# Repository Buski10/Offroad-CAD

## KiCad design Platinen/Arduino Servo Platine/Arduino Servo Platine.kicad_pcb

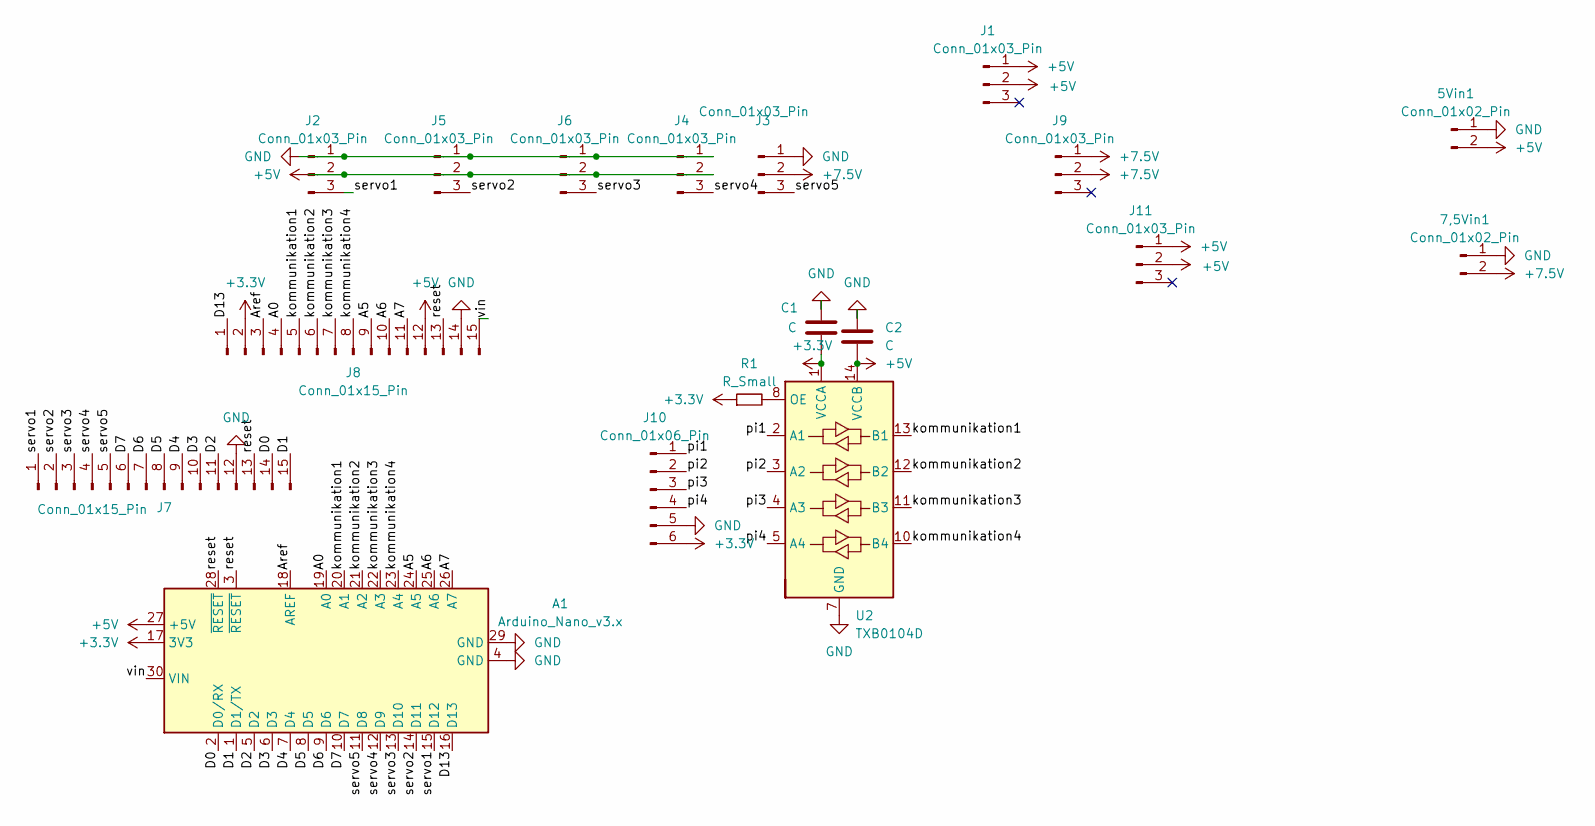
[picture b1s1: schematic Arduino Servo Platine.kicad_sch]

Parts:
5Vin1, 7,5Vin1: Conn_01x02_Pin; Molex_Micro-Fit_3.0_43650-0215_1x02_P3.00mm_Vertical
A1: Arduino_Nano_v3.x; Arduino_Nano
C1, C2: C; C_0805_2012Metric_Pad1.18x1.45mm_HandSolder
J1, J9, J11: Conn_01x03_Pin; SW_100SP1T1B1M1QEH
J2, J3, J4, J5, J6: Conn_01x03_Pin; JST_PH_B3B-PH-K_1x03_P2.00mm_Vertical
J7, J8: Conn_01x15_Pin; PinSocket_1x15_P2.54mm_Vertical
J10: Conn_01x06_Pin; JST_PH_B6B-PH-K_1x06_P2.00mm_Vertical
R1: R_Small; R_0805_2012Metric_Pad1.20x1.40mm_HandSolder
U2: TXB0104D; D14

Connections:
+3.3V: A1.17 (3V3), C1.2, J8.2, J10.6, R1.1, U2.1 (VCCA)
+5V: 5Vin1.2, A1.27 (+5V), C2.2, J1.1, J1.2, J2.2, J4.2, J5.2, J6.2, J8.12, J11.1, J11.2, U2.14 (VCCB)
+7.5V: 7,5Vin1.2, J3.2, J9.1, J9.2
/A0: A1.19 (A0), J8.4
/A5: A1.24 (A5), J8.9
/A6: A1.25 (A6), J8.10
/A7: A1.26 (A7), J8.11
/Aref: A1.18 (AREF), J8.3
/D0: A1.2 (D0/RX), J7.14
/D1: A1.1 (D1/TX), J7.15
/D2: A1.5 (D2), J7.11
/D3: A1.6 (D3), J7.10
/D4: A1.7 (D4), J7.9
/D5: A1.8 (D5), J7.8
/D6: A1.9 (D6), J7.7
/D7: A1.10 (D7), J7.6
/D13: A1.16 (D13), J8.1
/kommunikation1: A1.20 (A1), J8.5, U2.13 (B1)
/kommunikation2: A1.21 (A2), J8.6, U2.12 (B2)
/kommunikation3: A1.22 (A3), J8.7, U2.11 (B3)
/kommunikation4: A1.23 (A4), J8.8, U2.10 (B4)
/pi1: J10.1, U2.2 (A1)
/pi2: J10.2, U2.3 (A2)
/pi3: J10.3, U2.4 (A3)
/pi4: J10.4, U2.5 (A4)
/reset: A1.3 (~RESET), A1.28 (~RESET), J7.13, J8.13
/servo1: A1.15 (D12), J2.3, J7.1
/servo2: A1.14 (D11), J5.3, J7.2
/servo3: A1.13 (D10), J6.3, J7.3
/servo4: A1.12 (D9), J4.3, J7.4
/servo5: A1.11 (D8), J3.3, J7.5
/vin: A1.30 (VIN), J8.15
GND: 5Vin1.1, 7,5Vin1.1, A1.4 (GND), A1.29 (GND), C1.1, C2.1, J2.1, J3.1, J4.1, J5.1, J6.1, J7.12, J8.14, J10.5, U2.7 (GND)
unnamed: R1.2, U2.8 (OE)

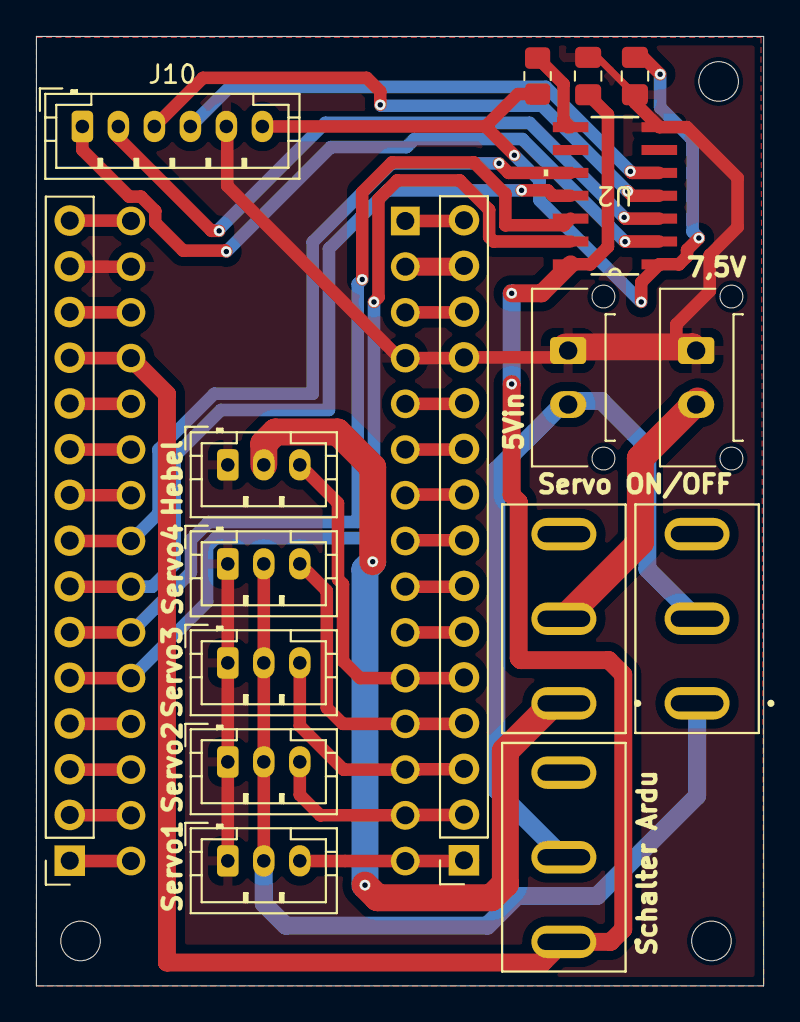
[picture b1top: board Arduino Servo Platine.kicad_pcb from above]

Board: 2 copper layers, 40.4 x 52.8 mm, 18 parts (1 on the bottom side), 34 nets.

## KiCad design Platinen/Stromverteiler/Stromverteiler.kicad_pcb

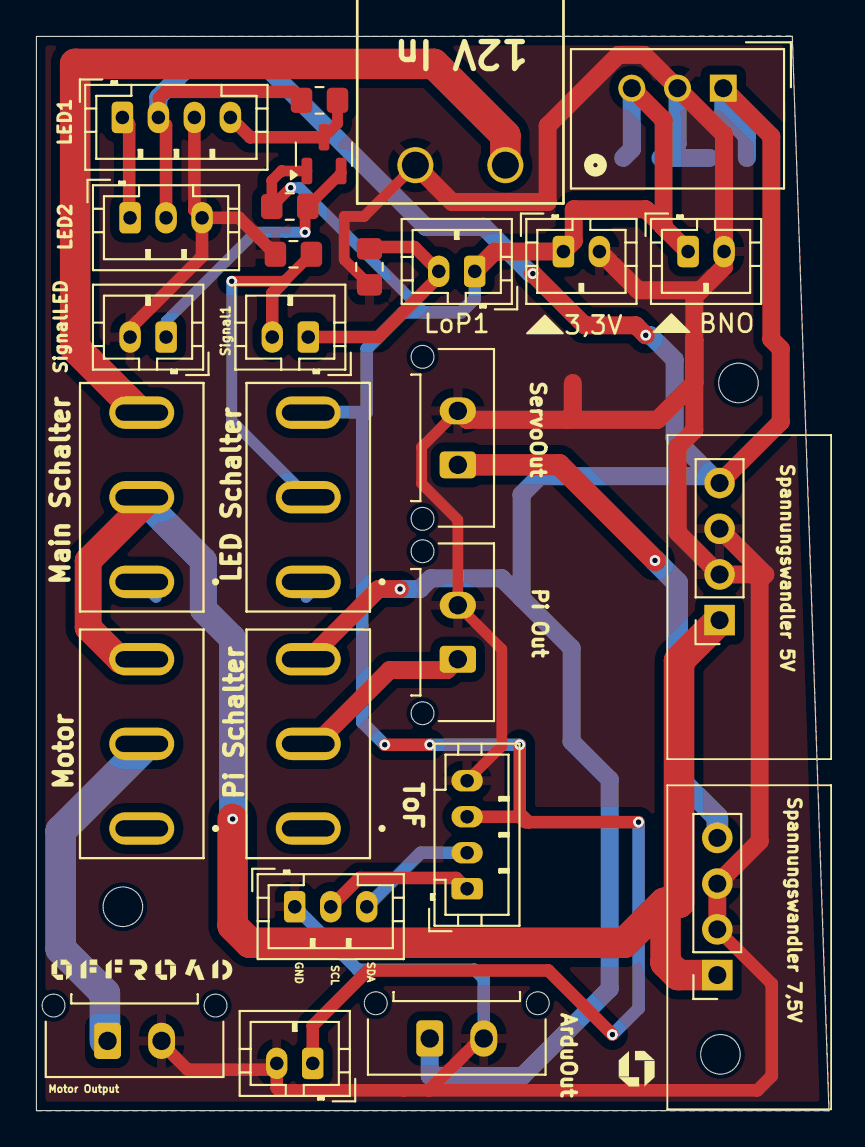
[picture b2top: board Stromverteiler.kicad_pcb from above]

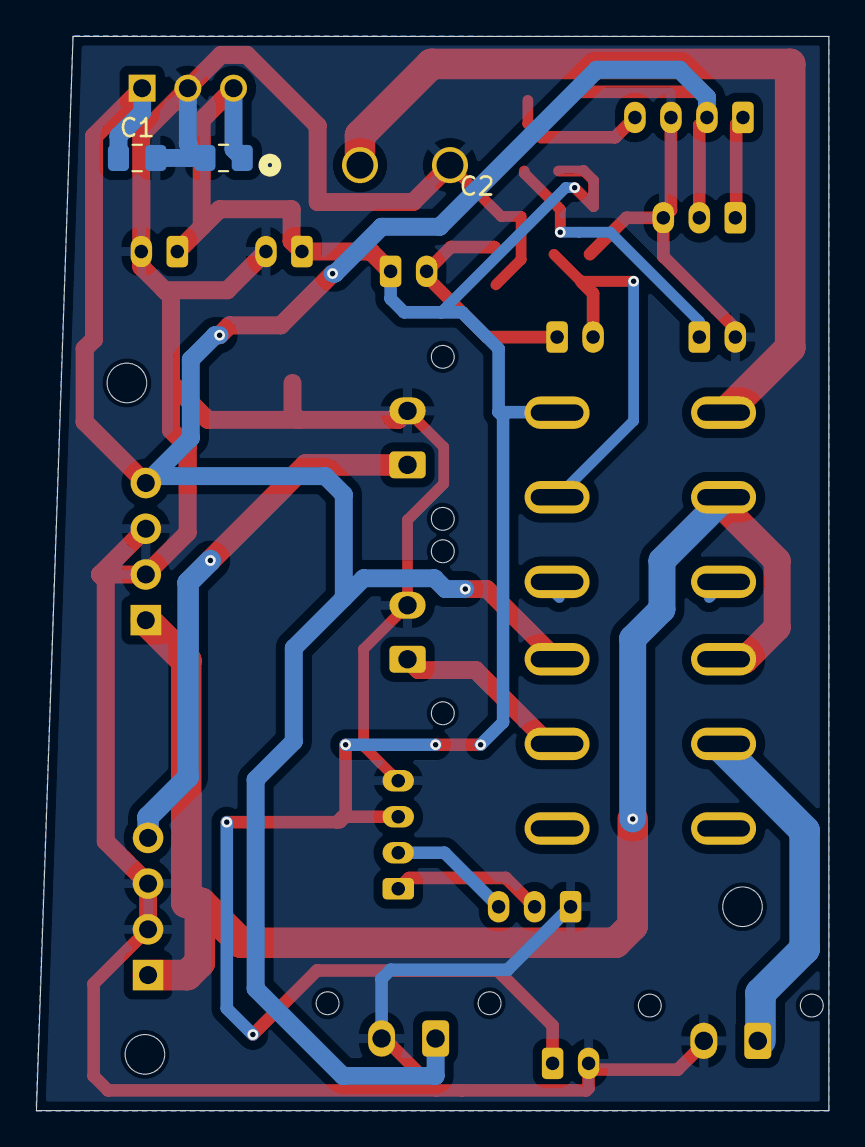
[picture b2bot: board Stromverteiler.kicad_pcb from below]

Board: 2 copper layers, 44.0 x 59.7 mm, 29 parts (2 on the bottom side), 12 nets.

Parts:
3,3V1: Conn_01x02_Pin; JST_PH_B2B-PH-K_1x02_P2.00mm_Vertical
3,3V2: 3,3out; JST_PH_B2B-PH-K_1x02_P2.00mm_Vertical
12Vin1: Conn_01x02_Pin; CONN_31330102_MZC
Arduino1: Conn_01x02_Pin; Molex_Micro-Fit_3.0_43650-0215_1x02_P3.00mm_Vertical
BNO1: Conn_01x02_Pin; JST_PH_B2B-PH-K_1x02_P2.00mm_Vertical
C1, C2: C; C_0805_2012Metric_Pad1.18x1.45mm_HandSolder
J1: Conn_01x03_Pin; JST_PH_B3B-PH-K_1x03_P2.00mm_Vertical
LEDAnzeige1: Conn_01x03_Pin; JST_PH_B3B-PH-K_1x03_P2.00mm_Vertical
LEDring1: Conn_01x04_Pin; JST_PH_B4B-PH-K_1x04_P2.00mm_Vertical
LoP1: Conn_01x02_Pin; JST_PH_B2B-PH-K_1x02_P2.00mm_Vertical
MotorOutput1: Conn_01x02_Pin; Molex_Micro-Fit_3.0_43650-0215_1x02_P3.00mm_Vertical
Output1: Conn_01x02_Pin; Molex_Micro-Fit_3.0_43650-0215_1x02_P3.00mm_Vertical
OutputPi1: Conn_01x02_Pin; Molex_Micro-Fit_3.0_43650-0215_1x02_P3.00mm_Vertical
Q1: BSS138; SOT-23
R1, R6, R7, R8: R_Small; R_0805_2012Metric_Pad1.20x1.40mm_HandSolder
Schalter1LED1, Schalter2Main1, Schalter3Motor1, Schalter4Pi1: Conn_01x03_Pin; SW_100SP1T1B1M1QEH
Signal1: Conn_01x02_Pin; JST_PH_B2B-PH-K_1x02_P2.00mm_Vertical
SignalLED1: Conn_01x02_Pin; JST_PH_B2B-PH-K_1x02_P2.00mm_Vertical
Spannungswandler1, Spannungswandler2: Conn_01x04_Pin; PinSocket_1x04_P2.54mm_Vertical
StemmaToF1: Conn_01x04_Pin; JST_PH_B4B-PH-K_1x04_P2.00mm_Vertical
Wandler1: TSR1-2433E; Converter_DCDC_TRACO_TSR1-xxxxE_THT

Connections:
+3.3V: 3,3V1.1, 3,3V2.1, BNO1.1, C2.2, LoP1.1, Q1.1 (G), R7.1, Schalter1LED1.3, StemmaToF1.3, Wandler1.3 (Vout)
+5V: Arduino1.1, C1.1, LEDAnzeige1.2, LEDring1.2, OutputPi1.1, R8.1, Schalter4Pi1.2, Schalter4Pi1.3, Spannungswandler1.4, Wandler1.1 (Vin)
+7.5V: Output1.1, Spannungswandler2.4
+12V: 12Vin1.1, MotorOutput1.1, Schalter2Main1.2, Schalter2Main1.3, Schalter3Motor1.2, Schalter3Motor1.3, Spannungswandler1.1, Spannungswandler2.1
GND: 3,3V1.2, 3,3V2.2, 12Vin1.2, Arduino1.2, BNO1.2, C1.2, C2.1, J1.1, LEDAnzeige1.3, LEDring1.3, MotorOutput1.2, Output1.2, OutputPi1.2, R1.2, R6.2, SignalLED1.2, Spannungswandler1.2, Spannungswandler1.3, Spannungswandler2.2, Spannungswandler2.3, StemmaToF1.4, Wandler1.2 (GND)
unnamed: J1.2, StemmaToF1.1
unnamed: J1.3, StemmaToF1.2
unnamed: LEDAnzeige1.1, LEDring1.1
unnamed: LEDring1.4, Q1.3 (D), R8.2
unnamed: LoP1.2, R1.1, Signal1.1
unnamed: Q1.2 (S), R7.2, SignalLED1.1
unnamed: R6.1, Schalter1LED1.2, Signal1.2

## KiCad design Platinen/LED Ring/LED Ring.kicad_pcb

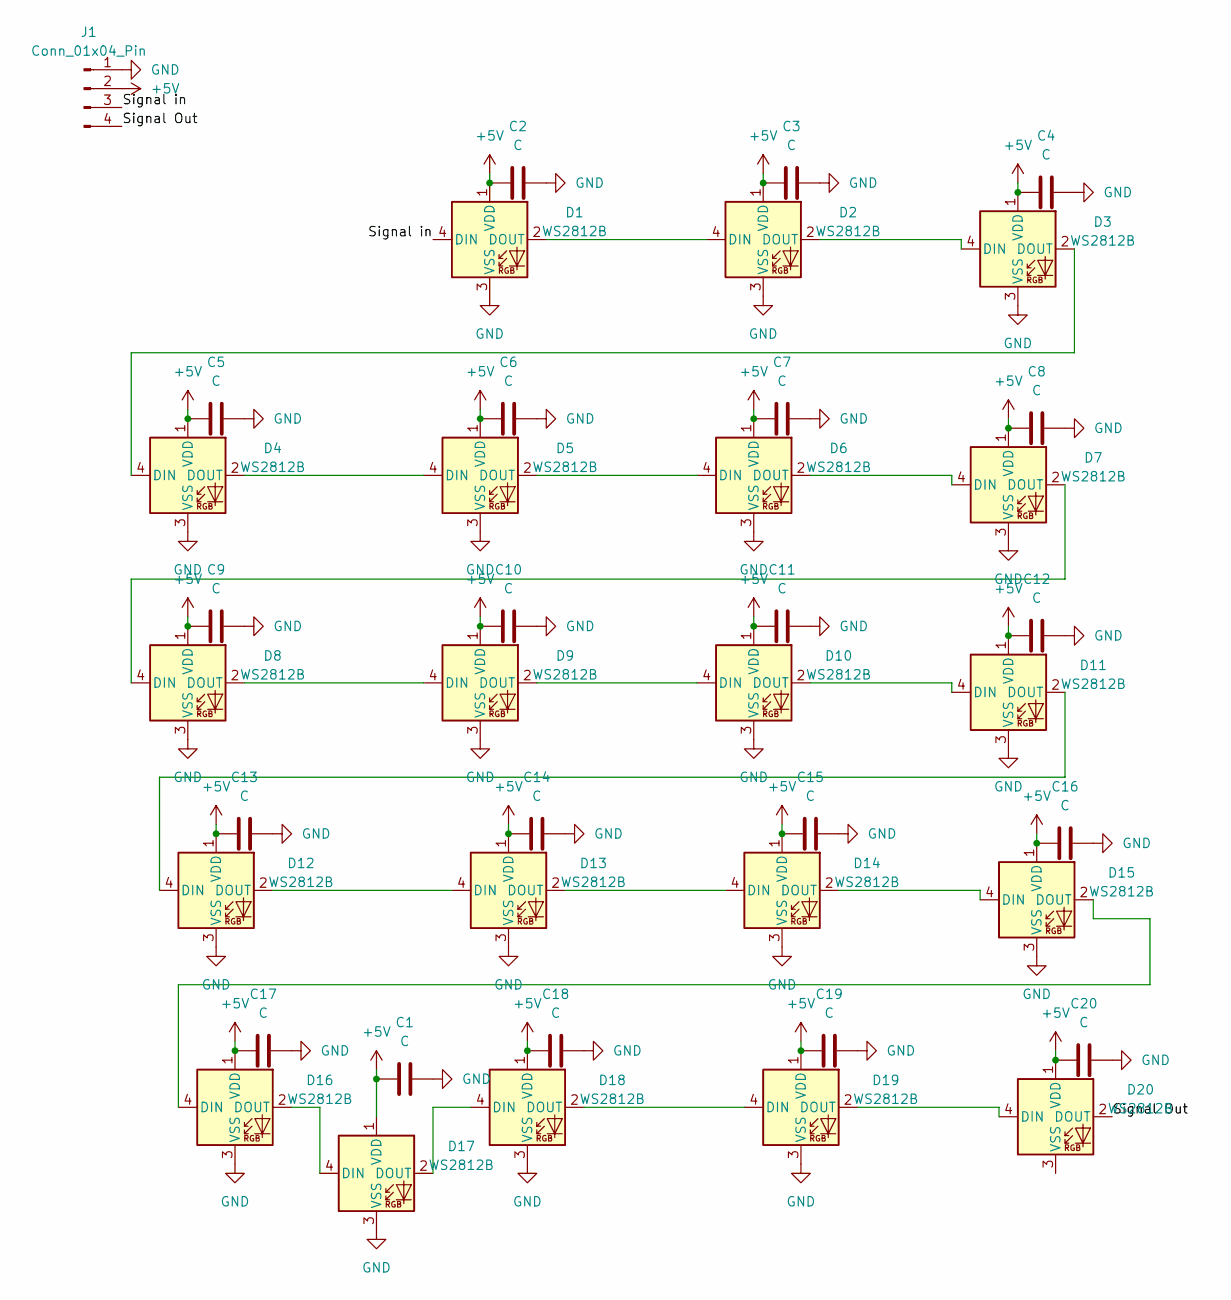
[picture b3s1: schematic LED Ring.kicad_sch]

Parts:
C1, C2, C3, C4, C5, C6, C7, C8, C9, C10, C11, C12, C13, C14, C15, C16, C17, C18, C19, C20: C; C_0805_2012Metric_Pad1.18x1.45mm_HandSolder
D1, D2, D3, D4, D5, D6, D7, D8, D9, D10, D11, D12, D13, D14, D15, D16, D17, D18, D19, D20: WS2812B; LED_WS2812B_PLCC4_5.0x5.0mm_P3.2mm
J1: Conn_01x04_Pin; JST_PH_B4B-PH-K_1x04_P2.00mm_Vertical

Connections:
+5V: C1.1, C2.1, C3.1, C4.1, C5.1, C6.1, C7.1, C8.1, C9.1, C10.1, C11.1, C12.1, C13.1, C14.1, C15.1, C16.1, C17.1, C18.1, C19.1, C20.1, D1.1 (VDD), D2.1 (VDD), D3.1 (VDD), D4.1 (VDD), D5.1 (VDD), D6.1 (VDD), D7.1 (VDD), D8.1 (VDD), D9.1 (VDD), D10.1 (VDD), D11.1 (VDD), D12.1 (VDD), D13.1 (VDD), D14.1 (VDD), D15.1 (VDD), D16.1 (VDD), D17.1 (VDD), D18.1 (VDD), D19.1 (VDD), D20.1 (VDD), J1.2
/Signal Out: D20.2 (DOUT), J1.4
/Signal in: D1.4 (DIN), J1.3
GND: C1.2, C2.2, C3.2, C4.2, C5.2, C6.2, C7.2, C8.2, C9.2, C10.2, C11.2, C12.2, C13.2, C14.2, C15.2, C16.2, C17.2, C18.2, C19.2, C20.2, D1.3 (VSS), D2.3 (VSS), D3.3 (VSS), D4.3 (VSS), D5.3 (VSS), D6.3 (VSS), D7.3 (VSS), D8.3 (VSS), D9.3 (VSS), D10.3 (VSS), D11.3 (VSS), D12.3 (VSS), D13.3 (VSS), D14.3 (VSS), D15.3 (VSS), D16.3 (VSS), D17.3 (VSS), D18.3 (VSS), D19.3 (VSS), J1.1
unnamed: D1.2 (DOUT), D2.4 (DIN)
unnamed: D2.2 (DOUT), D3.4 (DIN)
unnamed: D3.2 (DOUT), D4.4 (DIN)
unnamed: D4.2 (DOUT), D5.4 (DIN)
unnamed: D5.2 (DOUT), D6.4 (DIN)
unnamed: D6.2 (DOUT), D7.4 (DIN)
unnamed: D7.2 (DOUT), D8.4 (DIN)
unnamed: D8.2 (DOUT), D9.4 (DIN)
unnamed: D9.2 (DOUT), D10.4 (DIN)
unnamed: D10.2 (DOUT), D11.4 (DIN)
unnamed: D11.2 (DOUT), D12.4 (DIN)
unnamed: D12.2 (DOUT), D13.4 (DIN)
unnamed: D13.2 (DOUT), D14.4 (DIN)
unnamed: D14.2 (DOUT), D15.4 (DIN)
unnamed: D15.2 (DOUT), D16.4 (DIN)
unnamed: D16.2 (DOUT), D17.4 (DIN)
unnamed: D17.2 (DOUT), D18.4 (DIN)
unnamed: D18.2 (DOUT), D19.4 (DIN)
unnamed: D19.2 (DOUT), D20.4 (DIN)

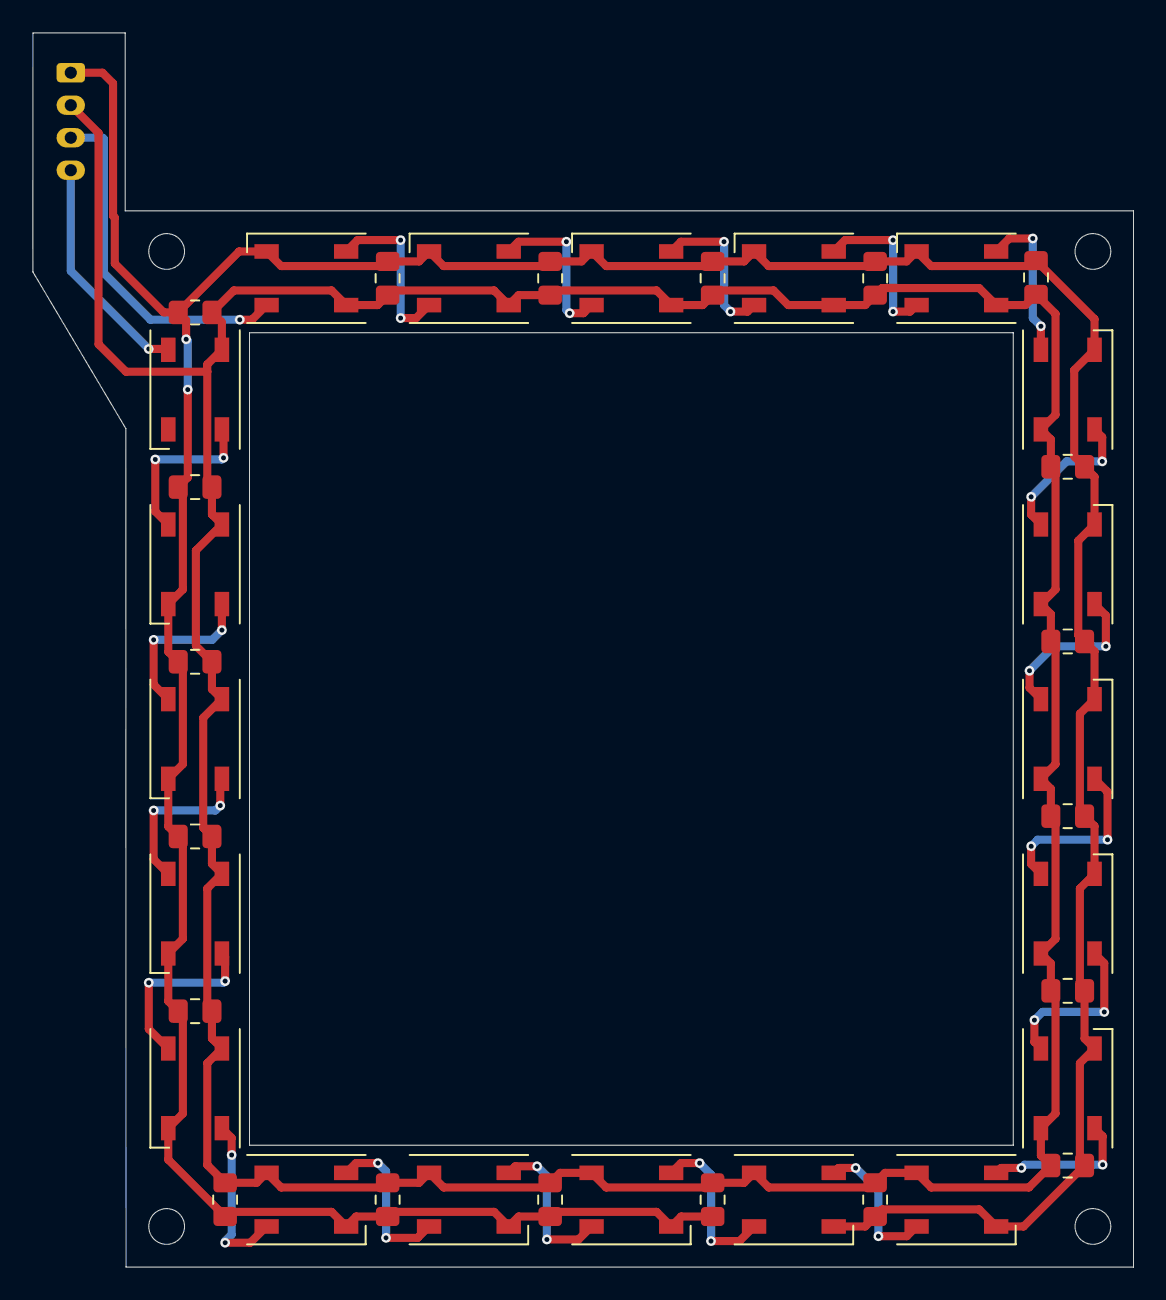
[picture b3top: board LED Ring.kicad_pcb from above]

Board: 2 copper layers, 67.7 x 76.0 mm, 41 parts (1 on the bottom side), 23 nets.

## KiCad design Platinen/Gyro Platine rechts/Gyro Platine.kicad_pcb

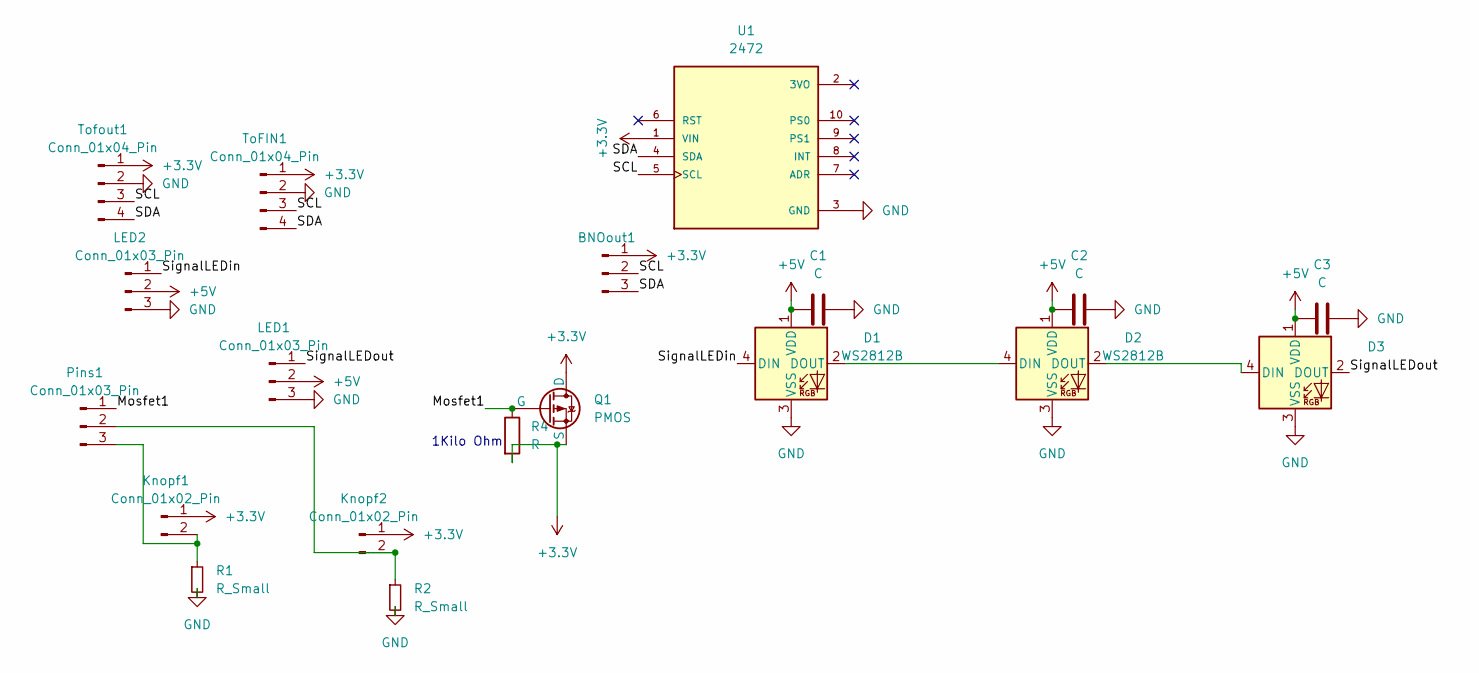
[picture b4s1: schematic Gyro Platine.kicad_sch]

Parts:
BNOout1: Conn_01x03_Pin; JST_PH_B3B-PH-K_1x03_P2.00mm_Vertical
C1, C2, C3: C; C_0805_2012Metric_Pad1.18x1.45mm_HandSolder
D1, D2, D3: WS2812B; LED_WS2812B_PLCC4_5.0x5.0mm_P3.2mm
Knopf1, Knopf2: Conn_01x02_Pin; JST_PH_B2B-PH-K_1x02_P2.00mm_Vertical
LED1, LED2: Conn_01x03_Pin; JST_PH_B3B-PH-K_1x03_P2.00mm_Vertical
Pins1: Conn_01x03_Pin; JST_PH_B3B-PH-K_1x03_P2.00mm_Vertical
Q1: PMOS; SOT-23_IRLML2244TRPBF_INF
R1, R2: R_Small; R_0805_2012Metric_Pad1.20x1.40mm_HandSolder
R4: R; R_0805_2012Metric_Pad1.20x1.40mm_HandSolder
ToFIN1: Conn_01x04_Pin; JST_PH_B4B-PH-K_1x04_P2.00mm_Vertical
Tofout1: Conn_01x04_Pin; JST_PH_B4B-PH-K_1x04_P2.00mm_Vertical
U1: 2472; MODULE_2472; PARTREV N/A

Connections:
+3.3V: BNOout1.1, Knopf1.1, Knopf2.1, Q1.1 (D), Q1.3 (S), R4.2, ToFIN1.1, Tofout1.1, U1.1 (VIN)
+5V: C1.1, C2.1, C3.1, D1.1 (VDD), D2.1 (VDD), D3.1 (VDD), LED1.2, LED2.2
/Mosfet1: Pins1.1, Q1.2 (G), R4.1
/SCL: BNOout1.2, ToFIN1.3, Tofout1.3, U1.5 (SCL)
/SDA: BNOout1.3, ToFIN1.4, Tofout1.4, U1.4 (SDA)
/SignalLEDin: D1.4 (DIN), LED2.1
/SignalLEDout: D3.2 (DOUT), LED1.1
GND: C1.2, C2.2, C3.2, D1.3 (VSS), D2.3 (VSS), D3.3 (VSS), LED1.3, LED2.3, R1.2, R2.2, ToFIN1.2, Tofout1.2, U1.3 (GND)
unnamed: D1.2 (DOUT), D2.4 (DIN)
unnamed: D2.2 (DOUT), D3.4 (DIN)
unnamed: Knopf1.2, Pins1.3, R1.1
unnamed: Knopf2.2, Pins1.2, R2.1

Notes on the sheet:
1Kilo Ohm

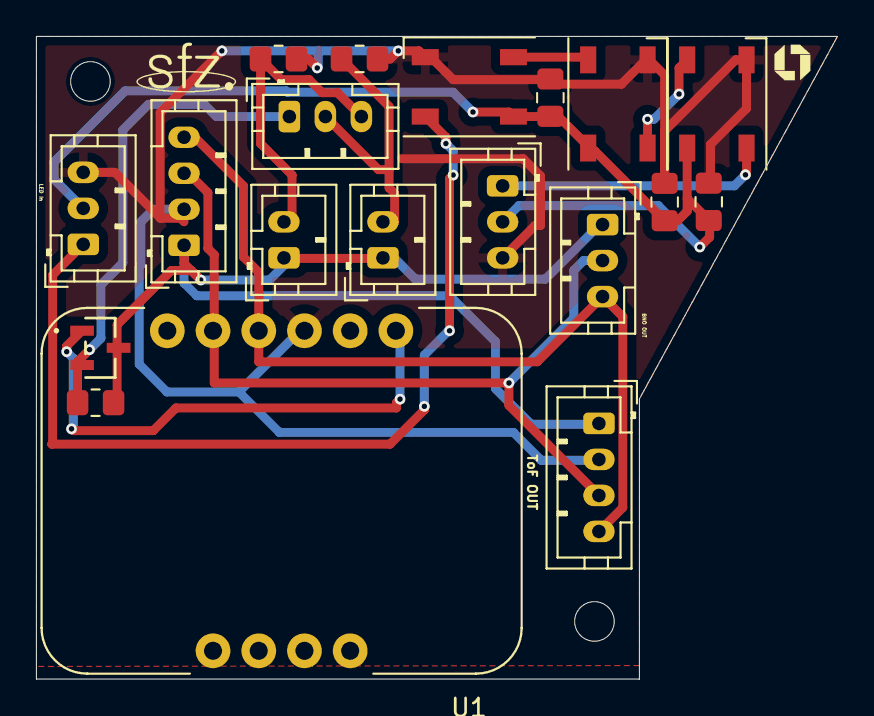
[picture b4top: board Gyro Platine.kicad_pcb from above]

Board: 2 copper layers, 44.5 x 35.7 mm, 19 parts (0 on the bottom side), 12 nets.

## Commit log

2025-10-28 Logo
2025-10-28 Add logo image to README file
2025-10-28 Add work in progress image to README
    Added a new image to indicate work in progress.
2025-10-28 workInProgress.png
2025-10-28 Update README with social media badges
    Added social media links for YouTube and Instagram.
